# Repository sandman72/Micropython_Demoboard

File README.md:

# MicroPython Demo Board

### What is the MicroPython DemoBoard?
This started out as a little PCB that we could use in our MicroPython Workshops. We quickly found out during the workshops that 
breadboarding sensors, buttons and other components took a lot of extra time, was prone to error and sometimes frustrating for beginners.
So I decided to create a PCB with some standard components that a Raspberry Pi Pico could be plugged into. No mess of wires anymore.

There is three areas that the workshops cover:

1. Building the hardware itself. Good for beginners and people that already know programming, but have no or little expirience with real hardware
2. Learning to program hardware with MicroPython on the hardware itself.
3. Have fun with the included games. ;)

This repo contains all necessary files for our MicroPython Hardware Workshop at the Attraktor e.V. Makerspace in Hamburg, Germany: 
<a href="https://wiki.attraktor.org/Micropython_Kurs_2023"> Attraktor MicroPython Workshop </a>

### Documentation:
I have provided extensive documentation about the build process, how to program with MicroPython and included a lot of examples.
You can find the documentation in the Docs directory:

English <a href="./Docs/MicroPython_Demoboard_V1.1_EN.pdf" target="_blank"> MicroPython Demo Board EN Doc (pdf) </a>

German  <a href="./Docs/MicroPython_Demoboard_V1.1_DE.pdf" target="_blank"> MicroPython Demo Board DE Doc (pdf) </a>

### Hardware:
The Demo Board works with a Raspberry Pi Pico WH plugged into the pinheaders and connects it to various sensors, buttons, LEDs and an OLED display.

#### Where can I get a board?
I have provided Gerber files to get your own boards produced under the releases tab on the right and in the hardware directory.

Sometimes "leftover" boards from our workshops can be found on <a href="https://www.ebay.de/usr/hellmann42" target="_blank"> my Ebay page</a>.

You can find an interactive BOM (Bill of Material) here: <a href="https://raw.githack.com/sandman72/micropython_demoboard/main/Hardware/MicroPython_DemoBoard_V1.1_iBOM.html" target="_blank"> iBOM </a>

#### Schematic and PCB Layout:

#### BEWARE: Due to the infamous Errata E7 bug I recommend to stick to the Rasperry Pi Pico RP2040 boards and not use the new Pi Pico 2 RP2350 based ones as the buttons will not work correctly.

### Firmware:
Included in the firmware directory is a board test file and the invaders game as self contained UF2 files.

Simply enter the bootsel mode (hold down the bootsel button, while plugging the Pi Pico in) and copy one for the firmwares over.

The default startup will enter a Menu where you can select games and board demos. Connect to the board with a MicroPython Editor like Thonny to programm.

### Software:
The software folder contains some demo scripts to try out the different sensors, buttons, buzzer, LEDs and display.

Included are some games like space invaders, flappy bird, snake and pong as well.

Also you'll find the test scripts there.

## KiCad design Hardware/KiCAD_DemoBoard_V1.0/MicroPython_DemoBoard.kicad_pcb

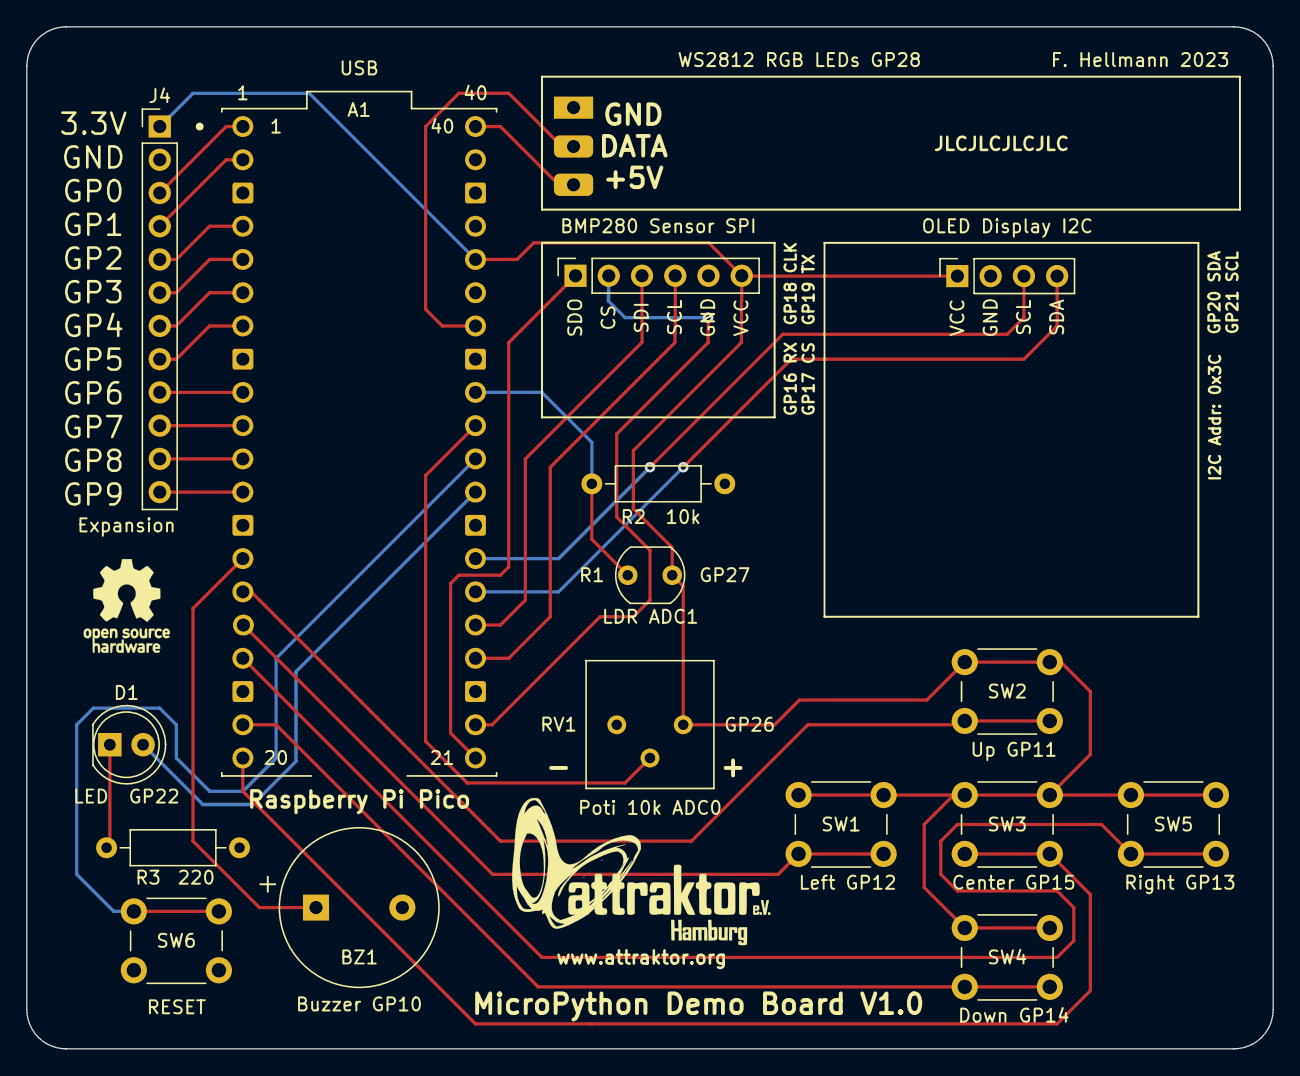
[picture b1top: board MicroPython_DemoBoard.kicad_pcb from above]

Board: 2 copper layers, 95.2 x 78.1 mm, 17 parts (0 on the bottom side), 31 nets.

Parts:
A1: Raspberry Pi Pico; Raspberry_Pi_Pico_W_SC0918
BZ1: Buzzer GP10; Buzzer_12x9.5RM7.6
D1: LED GP22; LED_D5.0mm
J1: WS2812 RGB LEDs GP28; PinHeader_1x03_P2.54mm_Vertical
J2: BMP280 Sensor SPI; PinSocket_1x06_P2.54mm_Vertical
J3: OLED Display I2C; PinSocket_1x04_P2.54mm_Vertical
J4: Expansion; PinHeader_1x12_P2.54mm_Vertical
R1: LDR ADC1; R_LDR_5.1x4.3mm_P3.4mm_Vertical
R2: 10k; R_Axial_DIN0207_L6.3mm_D2.5mm_P10.16mm_Horizontal
R3: 220; R_Axial_DIN0207_L6.3mm_D2.5mm_P10.16mm_Horizontal
RV1: Poti 10k ADC0; Potentiometer_Bourns_3386P_Vertical
SW1: Left GP12; SW_PUSH_6mm_H7.3mm
SW2: Up GP11; SW_PUSH_6mm_H7.3mm
SW3: Center GP15; SW_PUSH_6mm_H7.3mm
SW4: Down GP14; SW_PUSH_6mm_H7.3mm
SW5: Right GP13; SW_PUSH_6mm_H7.3mm
SW6: RESET; SW_PUSH_6mm_H7.3mm

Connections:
+3V3: A1.36 (3V3_OUT), J2.6, J3.1, J4.1, R1.1, RV1.3, SW1.1 (A), SW2.1 (A), SW3.1 (A), SW4.1 (A), SW5.1 (A)
+5V: A1.40 (VBUS), J1.3
/Center: A1.20 (GP15), SW3.2 (B)
/Down: A1.19 (GP14), SW4.2 (B)
/I2C SCL: A1.27 (GP21), J3.3
/I2C SDA: A1.26 (GP20), J3.4
/Left: A1.16 (GP12), SW1.2 (B)
/Right: A1.17 (GP13), SW5.2 (B)
/SPI CLK: A1.24 (GP18), J2.4
/SPI CS: A1.22 (GP17), J2.2
/SPI RX: A1.21 (GP16), J2.1
/SPI TX: A1.25 (GP19), J2.3
/Up: A1.15 (GP11), SW2.2 (B)
GND: A1.3 (GND), A1.8 (GND), A1.13 (GND), A1.18 (GND), A1.23 (GND), A1.28 (GND), A1.33 (AGND), A1.38 (GND), BZ1.2 (+), J1.1, J2.5, J3.2, J4.2, R2.2, R3.2, RV1.1, SW6.1 (A)
unnamed: A1.1 (GP0), J4.3
unnamed: A1.2 (GP1), J4.4
unnamed: A1.4 (GP2), J4.5
unnamed: A1.5 (GP3), J4.6
unnamed: A1.6 (GP4), J4.7
unnamed: A1.7 (GP5), J4.8
unnamed: A1.9 (GP6), J4.9
unnamed: A1.10 (GP7), J4.10
unnamed: A1.11 (GP8), J4.11
unnamed: A1.12 (GP9), J4.12
unnamed: A1.14 (GP10), BZ1.1 (-)
unnamed: A1.29 (GP22), D1.2 (A)
unnamed: A1.31 (GP26), RV1.2
unnamed: A1.32 (GP27), R1.2, R2.1
unnamed: A1.34 (GP28), J1.2
unnamed: A1.30 (RUN), SW6.2 (B)
unnamed: D1.1 (K), R3.1

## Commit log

2024-01-16 added files to repository
    first commit with
    hardware V1.0 (old OLED pinout) and V1.1 (new OLED pinout)
    software V1.0
    firmware V1.0 with board test and invader game
2024-01-16 Update README.md
    first commit
2024-01-16 Update README.md
    cosmetics
2024-01-16 Update 01_Blink_LED_Demo.py
    remove comments
2024-01-16 Update 02_PWM_LED_Demo.py
    change to sleep_ms
2024-01-16 Added Firmware Image
    Added Firmware Image with different Games
2024-01-16 Added Boot Menu
    Added Boot Menu for Games and Board Test.
2024-01-17 Update Flappy_Bird.py
    fixed bug: high_score variable not set on first run
2024-01-17 Add files via upload
    Firmware with bootloader for the FabCity e.V. boards
2024-06-11 MicroPython Crashkurs Firmware
2025-02-16 initial v1.1 upload
2025-02-16 Create LICENSE
